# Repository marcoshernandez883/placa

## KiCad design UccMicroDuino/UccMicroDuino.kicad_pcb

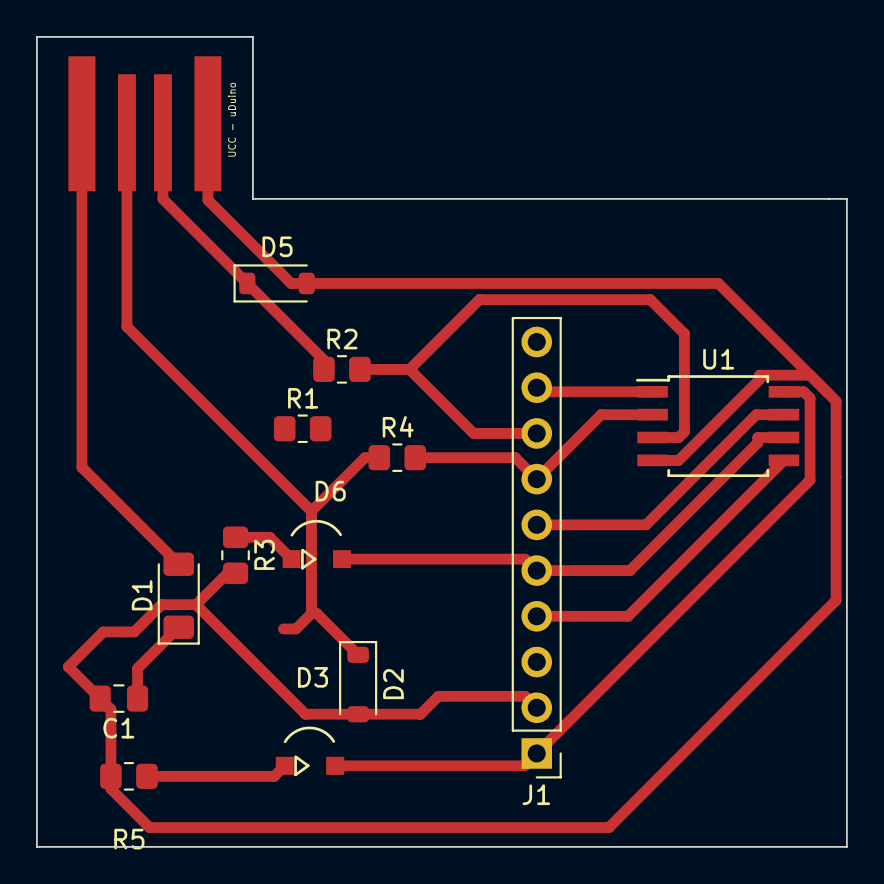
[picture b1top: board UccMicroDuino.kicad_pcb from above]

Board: 2 copper layers, 45.0 x 45.0 mm, 14 parts (0 on the bottom side), 13 nets.

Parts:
C1: C; C_0805_2012Metric_Pad1.18x1.45mm_HandSolder
D1: D_Filled; D_MiniMELF
D2, D5: D_Zener; D_SOD-123
D3, D6: LED; ledSMD
J1: Conn_01x10_Socket; PinHeader_1x10_P2.54mm_Vertical
J2: USB_A; USB_A_UCC
R1, R2, R3, R4, R5: R; R_0805_2012Metric_Pad1.20x1.40mm_HandSolder
U1: ATtiny85-20S; SOIC-8W_5.3x5.3mm_P1.27mm

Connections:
+5V: C1.1, D1.1 (K), D3.2 (A), J1.1, R1.1, U1.8 (VCC)
GND: C1.2, D2.2 (A), D5.2 (A), J1.2, J2.4 (GND), R3.2, R5.2, U1.4 (GND)
unnamed: D1.2 (A), J2.1 (VBUS)
unnamed: D2.1 (K), J2.2 (D-), R1.2, R4.1
unnamed: D3.1 (K), R5.1
unnamed: D5.1 (K), J2.3 (D+), R2.1
unnamed: D6.2 (A), J1.5, U1.6 (PB1)
unnamed: D6.1 (K), R3.1
unnamed: J1.4, U1.5 (AREF/PB0)
unnamed: J1.6, U1.7 (PB2)
unnamed: J1.7, R4.2, U1.2 (XTAL1/PB3)
unnamed: J1.8, R2.2, U1.3 (XTAL2/PB4)
unnamed: J1.9, U1.1 (~RESET/PB5)

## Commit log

2024-04-28 primer commit nasi
